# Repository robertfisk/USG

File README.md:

## The USG is Good, not Bad
The USG is a firewall for your USB ports, protecting your computer from [BadUSB](https://srlabs.de/badusb/). It connects between your computer and your untrusted USB device, isolating the badness and keeping your computer safe. 

#### For more info, hit [the Wiki](https://github.com/robertfisk/USG/wiki).

## v0.9 Firmware
This is the firmware branch for the USG v0.9, which is the DIY hardware assembled out of development boards. Learn how to [build your own USG here.](https://github.com/robertfisk/USG/wiki/Hardware-%28DIY-v0.9%29)

## USG v1.0 hardware
The USG v1.0 is available now from the [online store.](https://globotron.nz/)

## Need More Speed?
The USG is performance-limited due to its USB 1 hardware. If you need to transfer large files from flash drives and hard drives, you need [the Armadillo](https://globotron.nz/products/armadillo-hardware-usb-firewall) instead. Based on the USG's proven open-source technology, the Armadillo is a next-gen device operating at USB 2.0 speed. Available exclusively through the [online store.](https://globotron.nz/products/armadillo-hardware-usb-firewall)

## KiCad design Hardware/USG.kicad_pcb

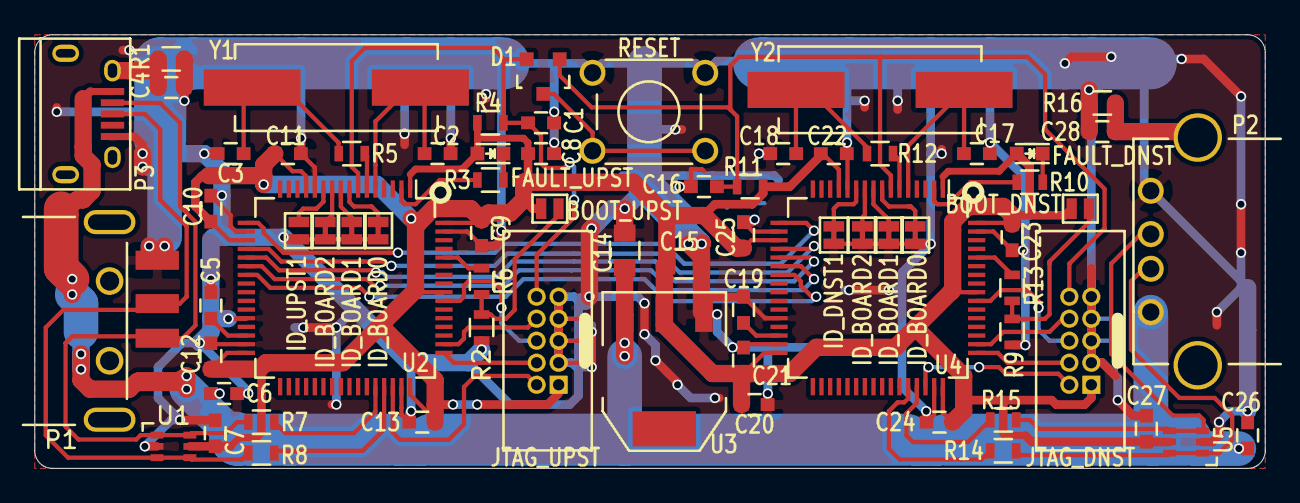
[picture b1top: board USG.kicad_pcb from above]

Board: 2 copper layers, 71.0 x 25.0 mm, 70 parts (0 on the bottom side), 53 nets.

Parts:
BOOT_DNST: Jumper_NO_Small; J_NO_0402
BOOT_UPST: Jumper_NO_Small; J_NO_0402
C1, C4, C6, C7, C9, C10, C11, C12, C13, C16, C21, C22, C23, C24, C25, C26, C27, C28: 0.1u; C_0603
C2, C3, C17, C18: 18p; C_0603
C5, C8, C19, C20: 4.7u; C_0603
C14: 10u; C_0805
C15: 22u; C_0805
D1: DOUBLE_DIODE_CCOM; SOT-23
FAULT_DNST: LED; LED-0603
FAULT_UPST: LED; LED-0603
ID_BOARD0, ID_BOARD0#2, ID_BOARD1, ID_BOARD1#2, ID_BOARD2, ID_BOARD2#2: Jumper_NC_Small; J_NC_0402
ID_DNST1: Jumper_NC_Small; J_NC_0402
ID_UPST1: Jumper_NO_Small; J_NO_0402
JTAG_DNST: CONN_02X05; Pin_Header_Straight_2x05_Pitch1.27mm
JTAG_UPST: CONN_02X05; Pin_Header_Straight_2x05_Pitch1.27mm
P1: USB_A_PLUG
P2: USB_A_SOCKET
P3: USB_OTG; USB_Micro-B
R1, R5, R12, R16: 220; R_0603
R2, R3, R9, R10: 1k; R_0603
R4, R6, R11, R13: 10k; R_0603
R7, R8, R14, R15: 22; R_0603
RESET: SW_PUSH; SW_TACT
U1, U5: NUP4114; SC-70-6
U2, U4: STM32F401xB; LQFP-64_10x10mm_Pitch0.5mm
U3: AZ1117CH-3.3; SOT-223
Y1, Y2: 8MHz; Crystal_HC49-SD_SMD

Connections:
+3V3: BOOT_DNST.2, BOOT_UPST.2, C7.1, C8.1, C9.2, C10.2, C11.2, C12.2, C13.2, C15.1, C20.1, C21.2, C22.2, C23.2, C24.2, C25.2, C27.1, FAULT_DNST.2, FAULT_UPST.2, JTAG_DNST.1, JTAG_UPST.1, R4.1, R11.1, U1.5, U2.1, U2.13, U2.19, U2.32, U2.48, U2.56, U2.64, U3.2, U4.1, U4.13, U4.19, U4.32, U4.48, U4.56, U4.64, U5.5
+5V: C6.1, C14.1, C26.1, P1.1, P2.1, P3.1, U3.3
/JTCK_DNST: JTAG_DNST.4, U4.49
/JTCK_UPST: JTAG_UPST.4, U2.49
/JTDI_DNST: JTAG_DNST.8, U4.50
/JTDI_UPST: JTAG_UPST.8, U2.50
/JTDO_DNST: JTAG_DNST.6, U4.55
/JTDO_UPST: JTAG_UPST.6, U2.55
/JTMS_DNST: JTAG_DNST.2, U4.46
/JTMS_UPST: JTAG_UPST.2, U2.46
/RESET_DNST: C16.1, D1.1, JTAG_DNST.10, R11.2, U4.7
/RESET_UPST: C1.1, D1.2, JTAG_UPST.10, R4.2, U2.7
/SPI_MISO: U2.22, U4.22
/SPI_MOSI: U2.23, U4.23
/SPI_NSS: U2.20, U4.20
/SPI_SCK: U2.21, U4.21
/SPI_TX_OK: U2.17, U4.17
GND: C1.2, C2.2, C3.2, C4.2, C5.2, C6.2, C7.2, C8.2, C9.1, C10.1, C11.1, C12.1, C13.1, C14.2, C15.2, C16.2, C17.2, C18.2, C19.2, C20.2, C21.1, C22.1, C23.1, C24.1, C25.1, C26.2, C27.2, C28.2, ID_BOARD0.1, ID_BOARD0#2.1, ID_BOARD1.1, ID_BOARD1#2.1, ID_BOARD2.1, ID_BOARD2#2.1, ID_DNST1.1, ID_UPST1.1, JTAG_DNST.3, JTAG_DNST.5, JTAG_DNST.7, JTAG_DNST.9, JTAG_UPST.3, JTAG_UPST.5, JTAG_UPST.7, JTAG_UPST.9, P1.4, P2.4, P3.5, R1.2, R2.2, R9.2, R16.2, RESET.1, U1.2, U2.12, U2.18, U2.28, U2.31, U2.47, U2.63, U3.1, U4.12, U4.18, U4.28, U4.31, U4.47, U4.63, U5.2
unnamed: BOOT_DNST.1, R9.1, R13.2
unnamed: BOOT_UPST.1, R2.1, R6.2
unnamed: C2.1, U2.5, Y1.1
unnamed: C3.1, R5.2, Y1.2
unnamed: C4.1, P1.5, P3.6, R1.1
unnamed: C5.1, U2.30
unnamed: C17.1, U4.5, Y2.1
unnamed: C18.1, R12.2, Y2.2
unnamed: C19.1, U4.30
unnamed: C28.1, P2.5, R16.1
unnamed: D1.3, RESET.2
unnamed: FAULT_DNST.1, R10.2
unnamed: FAULT_UPST.1, R3.2
unnamed: ID_DNST1.2, U4.11
unnamed: ID_BOARD0.2, U4.8
unnamed: ID_BOARD1.2, U4.9
unnamed: ID_BOARD2.2, U4.10
unnamed: ID_UPST1.2, U2.11
unnamed: ID_BOARD0#2.2, U2.8
unnamed: ID_BOARD1#2.2, U2.9
unnamed: ID_BOARD2#2.2, U2.10
unnamed: P1.2, P3.2, R7.1, U1.1, U1.6
unnamed: P1.3, P3.3, R8.1, U1.3, U1.4
unnamed: P2.2, R14.1, U5.1, U5.6
unnamed: P2.3, R15.1, U5.3, U5.4
unnamed: R3.1, U2.2
unnamed: R5.1, U2.6
unnamed: R6.1, U2.60
unnamed: R7.2, U2.44
unnamed: R8.2, U2.45
unnamed: R10.1, U4.2
unnamed: R12.1, U4.6
unnamed: R13.1, U4.60
unnamed: R14.2, U4.44
unnamed: R15.2, U4.45

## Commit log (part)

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2015-06-04 Initial commit!
    Upstream (device) firmware builds, emulates a small USB block device
    filled with zeroes.
2015-06-04 Add OpenOCD config file for Olimex STM32-H405 development board.
2015-07-17 Minor tweaks to downstream interface
2015-07-19 Fixed Eclipse's Debug and Release configurations
2015-07-21 Initial commit of Downstream template project.
2015-07-25 Continued polishing work on Downstream project.
2015-08-08 More refactoring in Upstream project
2015-08-08 Initial implementation of Downstream SPI interface and state machine.
2015-08-16 Full implementation of Downstream MSC interface, including significant modifications to USB host MSC.
    Also, minor tweaks to Upstream.
2015-08-20 Added priority elevation to Downstream USB host processing code that interacts with SPI.
    It elevates to USB_OTG priority to avoid preemption by SPI, DMA, or USB
    interrupts thus avoiding synchronisation issues between USB host stack
    and SPI interface.
    Also minor improvements to Downstream error handling.
2015-08-23 - Implement notification of Downstream USB device removal, and corresponding Upstream disconnection - Improve Upstream handling of TxOk signal from Downstream - Misc tweaks
2015-09-30 Crazy hardware issues, about to revert Upstream SPI from DMA to interrupt transfers
2015-10-02 IT. WORKS. !!!!!!!
2015-10-03 Increase SPI interface speed 4x, to 5.25Mbps. Required modifications to SPI peripheral library. At this speed SPI requires ~60% CPU time at -Og optimisation level. This could be further improved by t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
    Speed is now limited by Downstream's single-packet-per-URB restriction,
    to about 460kB/s. USB Middleware does not implement TX FIFO empty
    interrupt, so a bit of work is required here.
2015-10-03 Added Mozilla Public License information to file headers.
    Mozilla Public License v2.0 is compatible with the various licenses used
    by ST and ARM.
2015-10-04 Tidy up commented DMA init code
2015-10-04 Add images for wiki.
2015-10-12 Previous commit missed an unsupported-device-flash-LED check.
    NOTE: Downstream's full-speed host controller is flakey when connecting
    to low-speed devices. One mouse enumerates on only 50% of connection
    events, while another mouse enumerates on 90% of connections. Grrr.
2015-11-07 Changed Upstream and Downstream SPI transfers back to DMA. DMA works correctly now, either because SPI is in 16-bit mode, or because I found all the other bugs!
    Doubled SPI baudrate to 10.5Mbps. Transfer speed now limited (again) by
    Downstream's lack of FIFO buffering in the USB host controller.
    Also disabled DMA transaction half-complete interrupt in
    stm32f4xx_hal_dma.c, as it wasn't doing anything useful.
2015-11-11 Add missing option to clock configuration
2015-11-12 Initial commit of v1.0 hardware. Schematic done, layout in progress.
2015-11-12 Hardware v1.0 beta complete, ready for fabrication
2015-11-12 Modify firmware for v1.0 hardware with STM32F401RC micro: - Processor-specific header - Startup file - Linker script - Project settings - Debugger config script - Debugger project settings - Board re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
2015-11-14 USG v1.0 beta WORKS!!!!!11
    So apparently the STM32F401's SPI DMA is even more buggy than the 405's.
    Worked around an intermittent stall/timeout by busy-waiting Upstream's
    packet length transmission and reception, instead of DMA-ing it like the
    packet body. Ugh...
2015-11-14 Tidy up misc files and settings
2015-11-15 Doc image for H405 board cap fix
2015-11-18 Tidy up generated files
2015-11-18 Apply v1.0's upstream DMA workaround to v0.9. So it seems that under some circumstances the 405 is equally buggy as the 401!
    Work around an intermittent stall/timeout by busy-waiting Upstream's
    packet length transmission and reception, instead of DMA-ing it like the
    packet body. Ugh...
2015-11-21 Holy shit what an epic hardware bug.
    So there's a host controller hardware bug on the STM32F407 that
    manifests when writing to some FAT filesystems. Transactions will stop
    partway through a 512-byte write, and nothing can get them started
    again. We can avoid this by soft-resetting the AHB-interface state
    machines on every channel halt.
2015-12-07 Increase Downstream's host command timeout to 5 seconds. It turns out some flash drives can take up to 2 seconds to write a single block.
2015-12-09 Update Readme to point to the wiki
2016-01-02 Revert "Initial commit of ST Cube HID drivers"
    This reverts commit 08068c25d4e4ad86922be2490401426a021bdd1a.
2016-01-11 Tweak product strings again
2016-01-11 Tweak OpenOCD readme.
2016-01-11 Messing with debug configurations again.
    Our custom OpenOCD scripts are now linked directly into the Eclipse
    debug configurations. No need to manually copy the files into OpenOCD's
    script directory.
2016-01-15 Mouse Upstream code half-done.
2016-04-09 Work on Downstream HID support. Also a bunch of random tweaks.
2016-04-10 Downstream HID SPI interface done, untested.
2016-04-14 Restructure & bugfix Upstream HID. Still some issue with Downstream...
2016-04-15 Fixed bug in Upstream MSC. I have no idea why it worked before...
2016-04-16 Add HID files that went missing in merge
2016-04-25 Remove unused HID header
2016-04-25 More work on enumerating cheap POS mice, arrrrgh.
    Added timeout checks and retry functionality to control transaction
    state machine. But some times the device just won't talk, so we flash
    the fault LED slowly to give the user some clue about what happened.
2016-04-27 Implemented HID report parser. Untested!
2016-04-28 HID report parser now handles collections.
2016-04-30 Improved HID report parser compatibility
2016-05-03 Improve handling of >8bit input values
2016-05-08 HID class: handle host restart gracefully
2016-05-31 Implemented FIFO support in Downstream host, significant speed increase!
    Each USB transaction passed to the driver now consists of multiple
    64-byte packets. 8 packets when receiving, 4 packets when transmitting.
    The STM32 silicon bugs out when more than 4 packets are scheduled to
    write at a time :(
    Reads 1.0MB/sec, writes 967kB/sec, not CPU limited :)
2016-06-03 Ignore Mass Storage subclass, and try to talk with transparent SCSI anyway. This may or may not be helpful!
2016-07-13 Tweak USB descriptor strings
2016-07-27 Minor fix for startup hardware-detection function
2016-07-30 Tweak USB middleware to avoid compiler warning
2016-08-20 Fix for occasional timeout on writes...
    ...Downstream was not always changing state correctly after closely
    spaced interrupts.
    Also improve flash-write-lockout function to avoid dependency on
    optimisation level.
    Conflicts:
    Upstream/Src/interrupts.c
2016-08-27 Fix for occasional problem when attaching mouse after powerup.
    It turned out we were getting a "device disconnected" interrupt while
    waiting for the port to enable following reset. Simply ignoring the
    disconnect interrupt allows everything to work! WTF...
2016-09-01 Incomplete and untested implementation of keyboard support
2016-09-03 Keyboard support implemented, but not tested
2016-09-04 Incomplete and untested implementation of keyboard support
    Conflicts:
    Upstream/Upstream Debug.launch
2016-09-05 HID class handles host restart correctly
2016-10-02 After an epic battle, suspend/resume/wakeup is now supported.
    It turns out that suspend support on the STM32 USB core is buggy as
    heck. Host mode cannot resume after suspend, and device mode cannot
    receive resume or send wakeup signalling.
    I managed to fake resume support by keeping Downstream and our connected
    device running at full power, and simulating a wakeup event to the host
    by disconnecting/reconnecting Upstream from the host.
2016-10-22 Don't freakout when wakeup-from-sleep fails during keyboard report out.
2016-10-23 Correctly resume operation after HID device unplug/replug
2016-10-23 Startup LED flash is now asynchronous.
    Not only a faster startup process, but also catches some HID devices
    that only work if initialised within 500ms of powerup.
2016-10-24 Fix for Upstream JTAG lockout - don't execute WFI too soon!
2016-10-31 Flush HID endpoint on init.
    Fixes delayed HID events after failed wakeup attempt.
2016-12-16 Remove obsolete kicad library from beta 1 project
2017-03-06 Meaningless update to project settings file
2017-03-07 Another fix for occasional mass storage write freakouts.
    USB host controller sometimes incorrectly reports number of TX packets
    in queue.
2017-03-10 Change Upstream release build optimisation to -O3
2017-03-17 Tweak DFU doc image
2017-03-17 Remove obsolete doc images
2017-06-19 Implemented read-only option (Downstream only)
2017-06-20 Tweak write protect SCSI sense code
2017-07-22 Enable all config options by default
2017-08-21 HID keyboard bot detection mostly implemented. Needs more advanced LED flash code, and testing.
2017-10-23 Tweaks to HID keyboard bot detection
2017-11-20 Initial implementation of mouse bot detection
2017-11-20 Added error band comparison to velocity matching
2018-01-05 Implement mouse acceleration pulse timing. Doesn't work on realistic inputs.
2018-01-06 Tweaks to mouse jump detection
2018-01-07 Remove jiggle detector as the constant-acceleration detector already does the same job.
2018-01-08 Tweak keyboard lockout threshold
2018-01-08 Fix project build settings
2018-01-08 Implement random-movement credit in the constant acceleration detector.
    This makes it more forgiving of constant acceleration mid-movement, if
    the beginning of the movement looks random. Handy for mice that for some
    reason generate bot-like constant velocities.
2018-01-09 Reset mouse velocity history on each movement
2018-01-13 Support HID mouse reports with an ID header (Lenovo)
2018-01-15 Maintain constant acceleration counter for several seconds, on the assumption that a mouse bot would wait until the human stops using the mouse before starting to do anything bad.
2018-01-19 Jump detection now measures entire length of movement, not just the proportion above the jump velocity threshold.
    Also tweaked constant acceleration parameters.
2018-02-23 Allow longer constant-speed motion before blocking
2018-03-04 Fix for mechanical keyboards sending > 8 byte packets
2018-03-23 Increase JTAG reliability - hold reset active while connecting
2018-03-31 Disconnect on SCSI eject command from host
2018-03-31 Dont freak out if we get two suspend events in a row
2018-04-02 Don't overwrite array bounds when mass storage device reports > 2 LUNs
2018-04-28 Fixed eclipse project settings & debug configurations
    Conflicts:
    Downstream/.cproject
    Downstream/Downstream Debug.launch
    Downstream/Downstream Release.launch
    Upstream/.settings/language.settings.xml
    Upstream/Upstream Debug.launch
2018-08-24 Sanity-check Upstream MSC parameters received from Downstream
2019-01-26 Ignore Hardware folder
2019-02-06 Fix project settings for .bin file generation
2020-01-05 Retry control requests for slow flash drives
    Conflicts:
    Downstream/Middlewares/ST/STM32_USB_Host_Library/Core/Src/usbh_ctlreq.c
2020-01-05 Delay GetMaxLUN command by 100ms.
    Conflicts:
    Downstream/Middlewares/ST/STM32_USB_Host_Library/Class/MSC/Src/usbh_msc.c
2020-01-06 Correctly handle reads/writes after stop command issued.
    Also correctly report device disconnection if Upstream polls too slowly.
    Conflicts:
    Downstream/Src/downstream_statemachine.c
    Upstream/Middlewares/ST/STM32_USB_Device_Library/Class/MSC/Src/usbd_msc_scsi.c
2020-01-06 (add forgotten files)
    Conflicts:
    Upstream/Src/upstream_statemachine.c
2020-01-06 Implement read/write indication on the fault LEDs
    Conflicts:
    Downstream/Inc/build_config.h
    Downstream/Src/downstream_msc.c
    Downstream/Src/led.c
    Upstream/Inc/build_config.h
    Upstream/Src/led.c
2020-01-06 Correctly ignore bogus suspend messages on device reconnect
